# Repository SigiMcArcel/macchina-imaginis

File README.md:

# macchina-imaginis
several application and yocto layers for machina imaginis

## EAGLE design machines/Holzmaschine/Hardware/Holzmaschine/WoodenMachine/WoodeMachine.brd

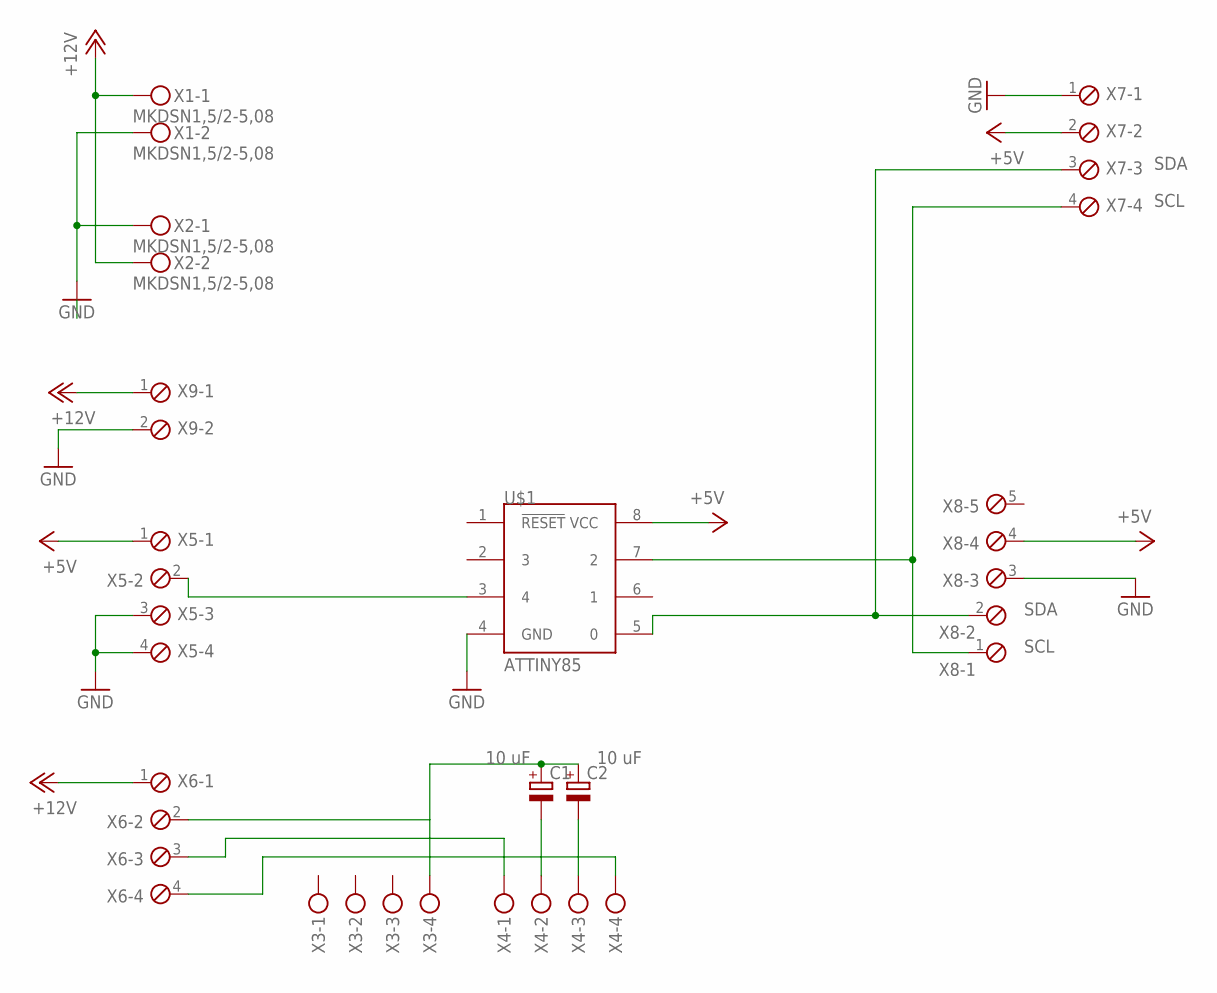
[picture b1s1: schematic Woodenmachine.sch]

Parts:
C1, C2: CPOL-EUE2.5-5; E2,5-5
U$1: ATTINY85; 8P3
X1, X2: MKDSN1,5/2-5,08
X3, X4: MKDSN1,5/4-5,08
X5, X6, X7: MPT4; 4POL254
X8: MPT5; 5POL254
X9: MPT2; 2POL254

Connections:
+5V: U$1.8 (VCC), X5.1, X7.2, X8.4
+12V: X1.1, X2.2, X6.1, X9.1
GND: U$1.4 (GND), X1.2, X2.1, X5.3, X5.4, X7.1, X8.3, X9.2
unnamed: U$1.3 (4), X5.2
unnamed: U$1.7 (2), X7.4, X8.1
unnamed: U$1.5 (0), X7.3, X8.2
unnamed: C1.+, C2.+, X3.4, X6.2
unnamed: C1.-, X4.2
unnamed: C2.-, X4.3
unnamed: X4.4, X6.4
unnamed: X4.1, X6.3

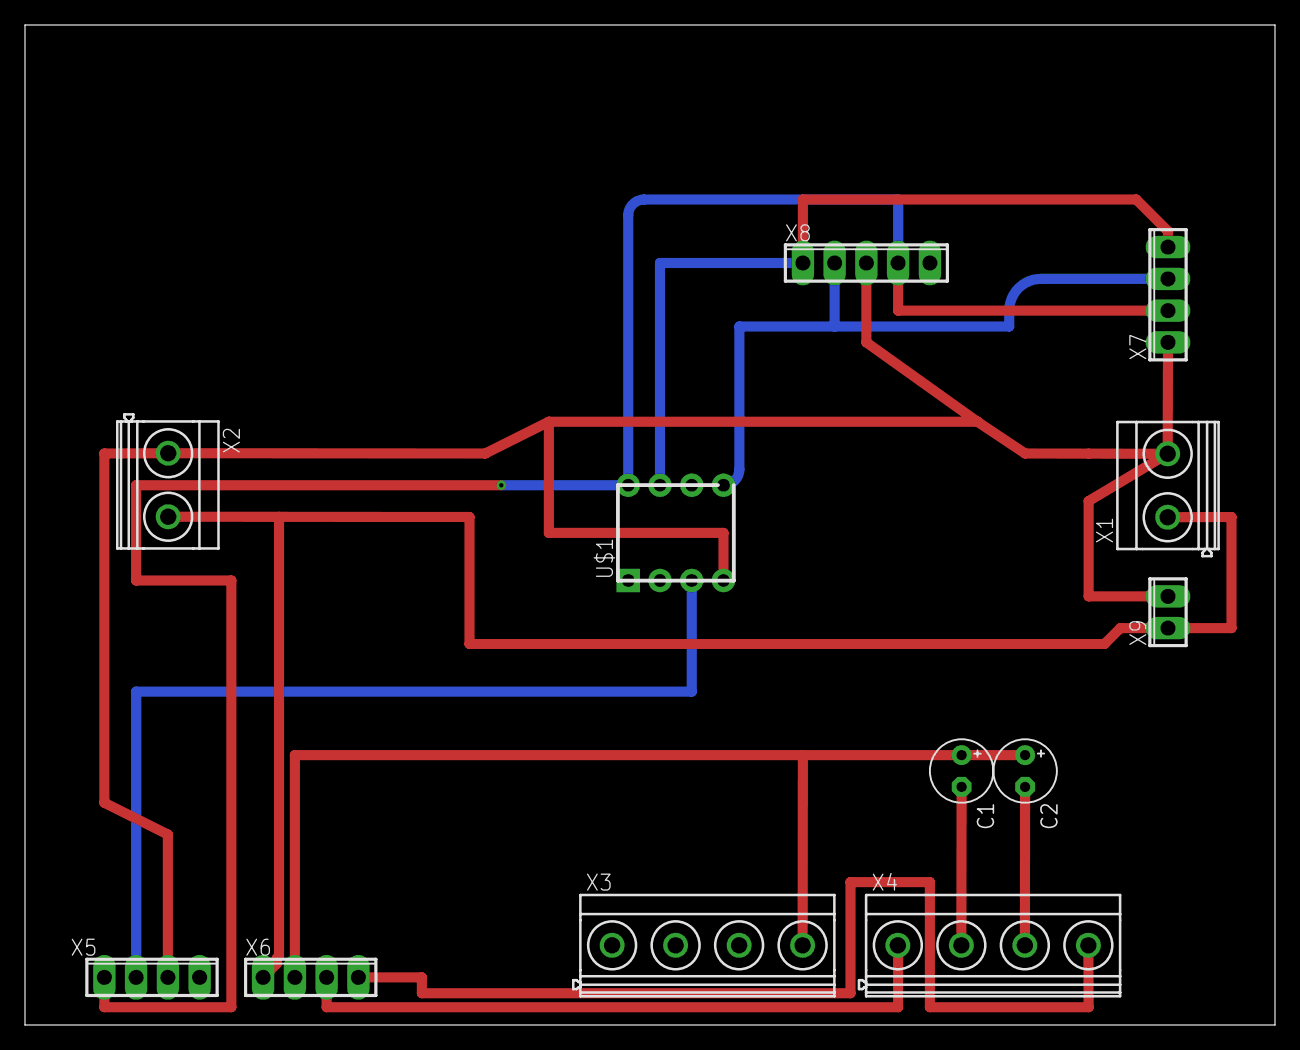
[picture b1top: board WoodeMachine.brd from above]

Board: 2 copper layers, 100.0 x 80.0 mm, 12 parts (0 on the bottom side), 11 nets.

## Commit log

2023-09-02 adding rubens csharp project and holzmaschine uc project
2023-09-04 tested and fixed
2023-10-14 improve potentiometer analog add wooden machine app
2023-10-15 test and bugfixes add makefile
2023-10-16 add missing library
2023-10-16 bugfix makefile
2023-10-21 add git ignore
2023-10-21 deamomize
2023-10-21 standard output
2023-10-21 mounting usb
2023-10-22 testing volume
2023-10-29 Poti : ADC no freerun Woddenmachine : bugfix wrong input output mapping
2023-11-01 Volume improving
2023-11-03 add schemata and board
2023-11-03 add platine board
2023-11-03 add platine schemata
2023-11-03 update manual
2023-11-03 set max volume to 80 %
2023-11-03 update docu
2023-11-14 add rubens
2023-11-18 - Leonardo board logic added - Adapt arduino prograam for raspberry rubens2
2023-11-25 - test and bugfix - adapt makefile
2023-11-25 added
2023-11-25 bugfix
2023-11-26 -Lamp play completed
2023-11-26 - bugfix start sequence, cleanup
2024-10-02 blob was to big
2024-10-05 Test and bugfixes, fix ledstrips ,emergency stop, and lampcontrol
2024-10-06 Test and Bugfix's, add ini file
2024-10-07 Set timings,bugfixes, cleanup
2024-10-13 Redesign Tasks and timimings, bugfixes
2024-10-13 uniform volume control
2024-10-14 Add missing files
2024-10-14 Add Offset setable
2024-10-14 soundpath with cmdline
2024-10-14 Bugfix sound path
2024-10-14 fix default values
2024-10-23 add twitternachine
2024-11-02 finish TwitterMachine update QuadratMachine
2024-11-03 update Audio constructor
2024-11-03 improve audio volume settings change sound folder
2024-11-04 update qudrat machine
